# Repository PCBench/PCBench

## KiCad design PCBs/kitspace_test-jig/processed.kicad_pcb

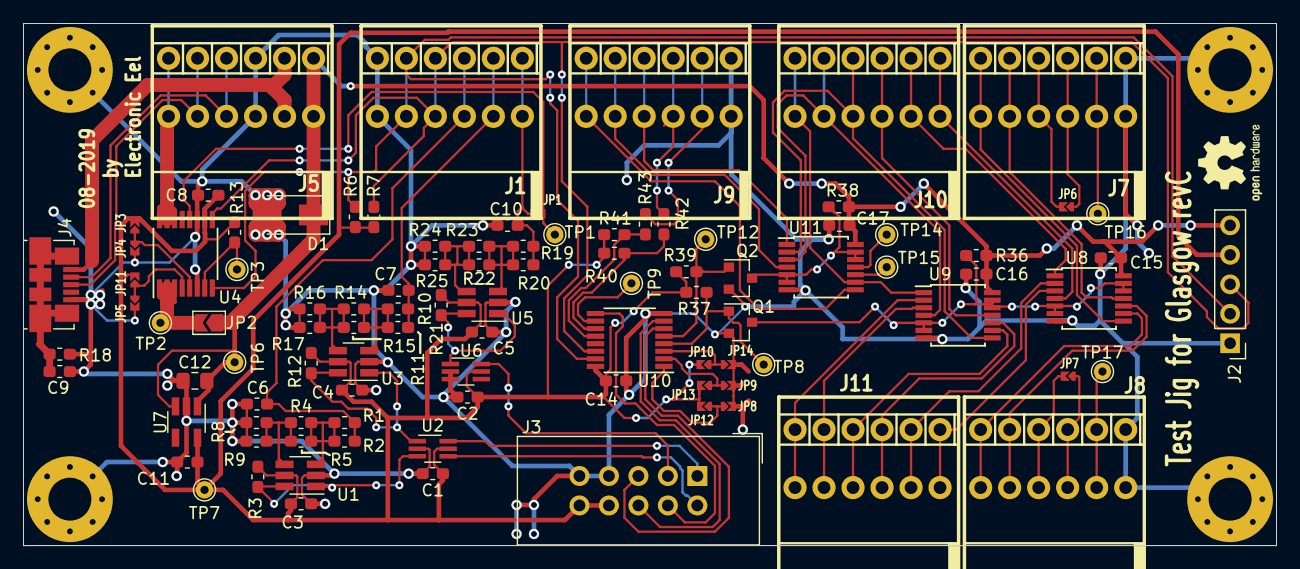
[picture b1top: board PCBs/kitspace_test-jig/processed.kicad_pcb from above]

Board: 2 copper layers, 108.0 x 45.0 mm, 103 parts (0 on the bottom side), 72 nets.

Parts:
C1, C2, C3, C4, C5, C6, C7, C8, C9, C10, C14, C15, C16, C17: 100nF; C_0603_1608Metric_Pad1.05x0.95mm_HandSolder
C11: 1µF; C_0603_1608Metric_Pad1.05x0.95mm_HandSolder
C12: 4.7µF; C_0805_2012Metric_Pad1.15x1.40mm_HandSolder
D1: SMAJ5A; D_SMA
H1, H2, H3, H4: MountingHole_Pad; MountingHole_3.7mm_Pad_Via
J1, J5, J7, J8, J9, J10, J11: AST04106; TerminalBlock_MetzConnect_AST04106_1x06_Lever_Clamp_45Degree
J2: DNP; PinHeader_1x05_P2.54mm_Vertical
J3: Conn_02x05_Odd_Even; IDC-Header_2x05_P2.54mm_Vertical
J4: USB_B_Micro; USB_Micro-B_Molex_47346-0001
JP1, JP4, JP5, JP6, JP7, JP8, JP9, JP10: SolderJumper_2_Bridged; Solderbridge-small-2pad
JP2: SolderJumper_2_Bridged; SolderJumper-2_P1.3mm_Open_TrianglePad1.0x1.5mm
JP3, JP11, JP12, JP13, JP14: SolderJumper_2_Open; Solderbridge-small-2pad
Q1, Q2: BSS138; SOT-23
R1: 5M1; R_0603_1608Metric_Pad1.05x0.95mm_HandSolder
R2: 68k; R_0603_1608Metric_Pad1.05x0.95mm_HandSolder
R3, R12, R13, R21: 4k7; R_0603_1608Metric_Pad1.05x0.95mm_HandSolder
R4, R8, R16, R22, R24, R40, R41, R42, R43: DNP; R_0603_1608Metric_Pad1.05x0.95mm_HandSolder
R5: 910R; R_0603_1608Metric_Pad1.05x0.95mm_HandSolder
R6, R7: 22k; R_0603_1608Metric_Pad1.05x0.95mm_HandSolder
R9: 33k; R_0603_1608Metric_Pad1.05x0.95mm_HandSolder
R10: 91k; R_0603_1608Metric_Pad1.05x0.95mm_HandSolder
R11: 3M6; R_0603_1608Metric_Pad1.05x0.95mm_HandSolder
R14: 1k; R_0603_1608Metric_Pad1.05x0.95mm_HandSolder
R15: 470R; R_0603_1608Metric_Pad1.05x0.95mm_HandSolder
R17: 12k; R_0603_1608Metric_Pad1.05x0.95mm_HandSolder
R18: 1M; R_0603_1608Metric_Pad1.05x0.95mm_HandSolder
R19: 510k; R_0603_1608Metric_Pad1.05x0.95mm_HandSolder
R20: 110k; R_0603_1608Metric_Pad1.05x0.95mm_HandSolder
R23: 680; R_0603_1608Metric_Pad1.05x0.95mm_HandSolder
R25: 7k5; R_0603_1608Metric_Pad1.05x0.95mm_HandSolder
R36, R38: 2k2; R_0603_1608Metric_Pad1.05x0.95mm_HandSolder
R37, R39: 100K; R_0603_1608Metric_Pad1.05x0.95mm_HandSolder
TP1, TP2, TP3, TP6, TP7, TP8, TP9, TP12, TP14, TP15, TP16, TP17: TestPoint; TestPoint_THTPad_D1.5mm_Drill0.7mm
U1, U3, U5: TPS3700; SOT-23-6_Handsoldering
U2, U6: 74LVC2G14; SOT-363_SC-70-6_Handsoldering
U4: INA260; TSSOP-16_4.4x5mm_P0.65mm
U7: AP2127K-3.3; SOT-23-5_HandSoldering
U8, U9, U11: 74HC4066; TSSOP-14_4.4x5mm_P0.65mm
U10: TCA9534; TSSOP-16_4.4x5mm_P0.65mm

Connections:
+3V3: C1.1, C2.1, C3.1, C4.1, C5.1, C8.1, C11.1, C14.1, J2.4, J3.8, J3.10, JP3.2, JP10.2, JP11.2, JP12.2, JP13.2, R3.1, R6.1, R7.1, R12.1, R13.1, R21.1, R37.1, R39.1, R40.2, R41.2, TP7.1, U1.5, U2.5, U3.5, U4.10, U5.5, U6.5, U7.5, U10.16
/DUT_Supply: J5.6, U4.14, U4.15, U4.16
/LED_1V2: J3.2, U2.4
/LED_3V3: J3.1, U2.6
/LED_5V: J3.3, U6.6
/LED_FAIL: J3.6, U10.7
/LED_PASS: J3.5, U10.6
/LED_RUN: J3.4, U10.9
/SCL: J1.4, J2.3, R7.2, U4.9, U10.14
/SDA: J1.5, J2.2, R6.2, U4.8, U10.15
/TP_1V2: C6.1, J1.3, R1.1, R2.1
/TP_3V3: C7.1, J1.2, R10.1, R11.1
/TP_5V: C10.1, J1.1, JP1.1, R19.1, R20.1
/port-connection/Aux_conn_ctrl_5V: Q2.3, R38.2, U11.5, U11.6, U11.12, U11.13
/port-connection/JIG_GPIO0: J9.3, R42.2
/port-connection/JIG_GPIO1: J9.2, R43.2
/port-connection/Port_conn_ctrl_5V: Q1.3, R36.2, U8.5, U8.6, U8.12, U8.13, U9.5, U9.6, U9.12, U9.13
/port-connection/TP_A0: J10.6, U9.1, U11.9
/port-connection/TP_A1: J10.5, U9.4, U11.3
/port-connection/TP_A2: J10.4, U9.8, U11.2
/port-connection/TP_A3: J10.3, U9.11
/port-connection/TP_A4: J10.2, U8.1
/port-connection/TP_A5: J10.1, U8.4
/port-connection/TP_A6: J7.6, U8.8
/port-connection/TP_A7: J7.5, U8.11
/port-connection/TP_A_Vio: J7.4, JP6.2
/port-connection/TP_A_Vsns: J7.3, JP6.1
/port-connection/TP_Aux_A10: J9.5, U11.4
/port-connection/TP_Aux_C9: J9.4, U11.1
/port-connection/TP_B0: J11.6, U9.2
/port-connection/TP_B1: J11.5, U9.3
/port-connection/TP_B2: J11.4, U9.9
/port-connection/TP_B3: J11.3, U9.10
/port-connection/TP_B4: J11.2, U8.2
/port-connection/TP_B5: J11.1, U8.3
/port-connection/TP_B6: J8.6, U8.9
/port-connection/TP_B7: J8.5, U8.10
/port-connection/TP_B_Vio: J8.4, JP7.2
/port-connection/TP_B_Vsns: J8.3, JP7.1
/port-connection/TP_Sync: J9.6, U11.8
/port-connection/~Aux_conn_ctrl: Q2.1, R39.2, TP12.1, U10.5
/port-connection/~Port_conn_ctrl: Q1.1, R37.2, TP8.1, U10.4
GND: C1.2, C2.2, C3.2, C4.2, C5.2, C6.2, C7.2, C8.2, C9.2, C10.2, C11.2, C12.2, C14.2, C15.2, C16.2, C17.2, D1.2, H1.1, H2.1, H3.1, H4.1, J1.6, J2.1, J3.7, J3.9, J4.5, J5.3, J7.1, J8.1, J9.1, JP4.2, JP5.2, JP8.2, JP9.2, JP14.2, Q1.2, Q2.2, R8.2, R9.2, R16.2, R17.2, R18.2, R24.2, R25.2, U1.2, U2.2, U3.2, U4.6, U4.11, U5.2, U6.2, U6.3, U7.2, U8.7, U9.7, U10.8, U11.7
unnamed: C9.1, J4.6, R18.1
unnamed: J4.1, J5.2
unnamed: J4.2, J5.4
unnamed: J4.3, J5.5
unnamed: J7.2, TP16.1
unnamed: J8.2, TP17.1
unnamed: JP1.2, TP1.1, U4.12
unnamed: JP2.2, TP2.1, U4.1, U4.2, U4.3
unnamed: JP3.1, JP4.1, U4.5
unnamed: JP10.1, JP14.1, U10.3
unnamed: JP5.1, JP11.1, U4.4
unnamed: JP8.1, JP12.1, U10.1
unnamed: JP9.1, JP13.1, U10.2
unnamed: R1.2, R2.2, R4.1, R5.1, U1.3
unnamed: R3.2, U1.1, U1.6, U2.3
unnamed: R4.2, R5.2, R8.1, R9.1, U1.4
unnamed: R10.2, R11.2, R14.1, R15.1, U3.3
unnamed: R12.2, U2.1, U3.1, U3.6
unnamed: R13.2, TP3.1, U4.7
unnamed: R14.2, R15.2, R16.1, R17.1, U3.4
unnamed: R19.2, R20.2, R22.1, R23.1, U5.3
unnamed: R21.2, U5.1, U5.6, U6.1
unnamed: R22.2, R23.2, R24.1, R25.1, U5.4
unnamed: R40.1, R42.1, U10.11
unnamed: R41.1, R43.1, U10.12
unnamed: TP9.1, U10.10
unnamed: TP14.1, U11.11
unnamed: TP15.1, U11.10
VBUS: C12.1, C15.1, C16.1, C17.1, D1.1, J2.5, J5.1, JP2.1, R36.1, R38.1, TP6.1, U7.1, U7.3, U8.14, U9.14, U11.14

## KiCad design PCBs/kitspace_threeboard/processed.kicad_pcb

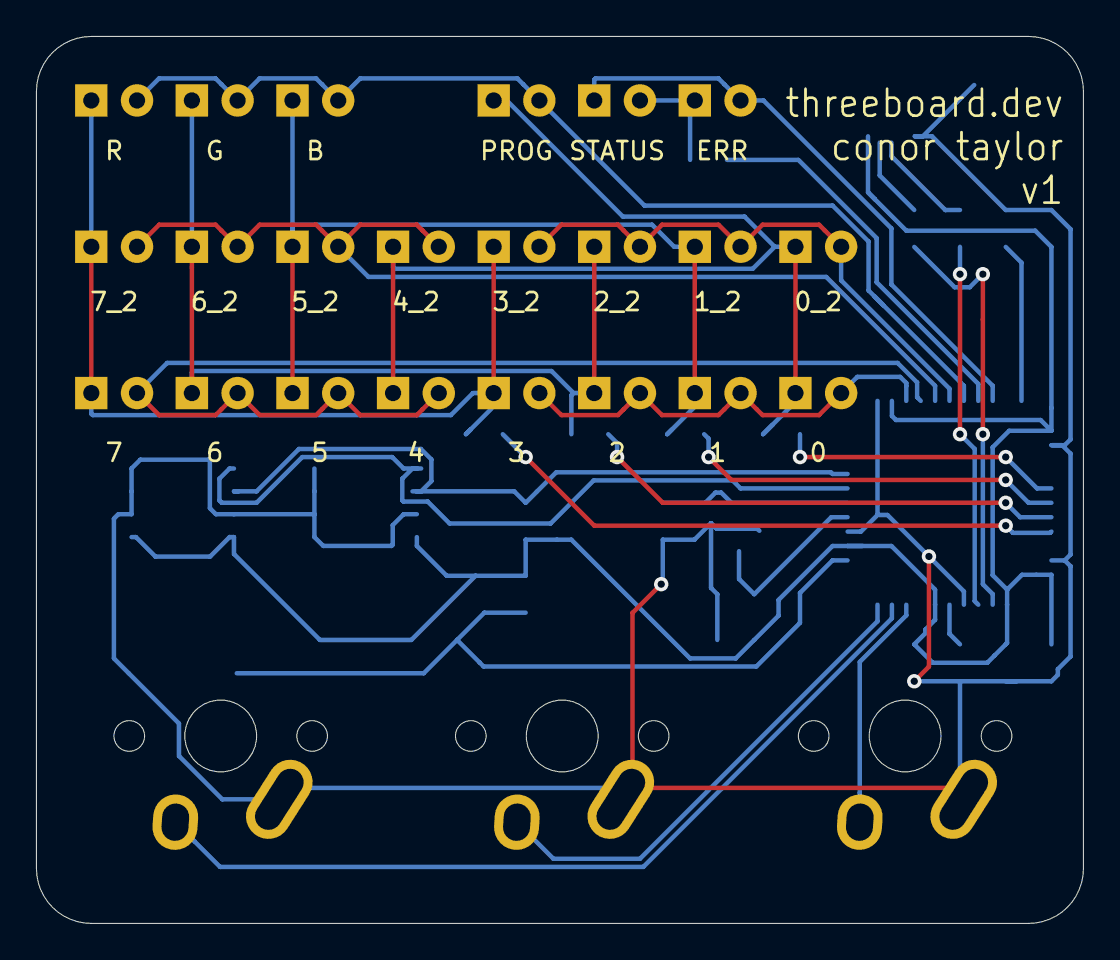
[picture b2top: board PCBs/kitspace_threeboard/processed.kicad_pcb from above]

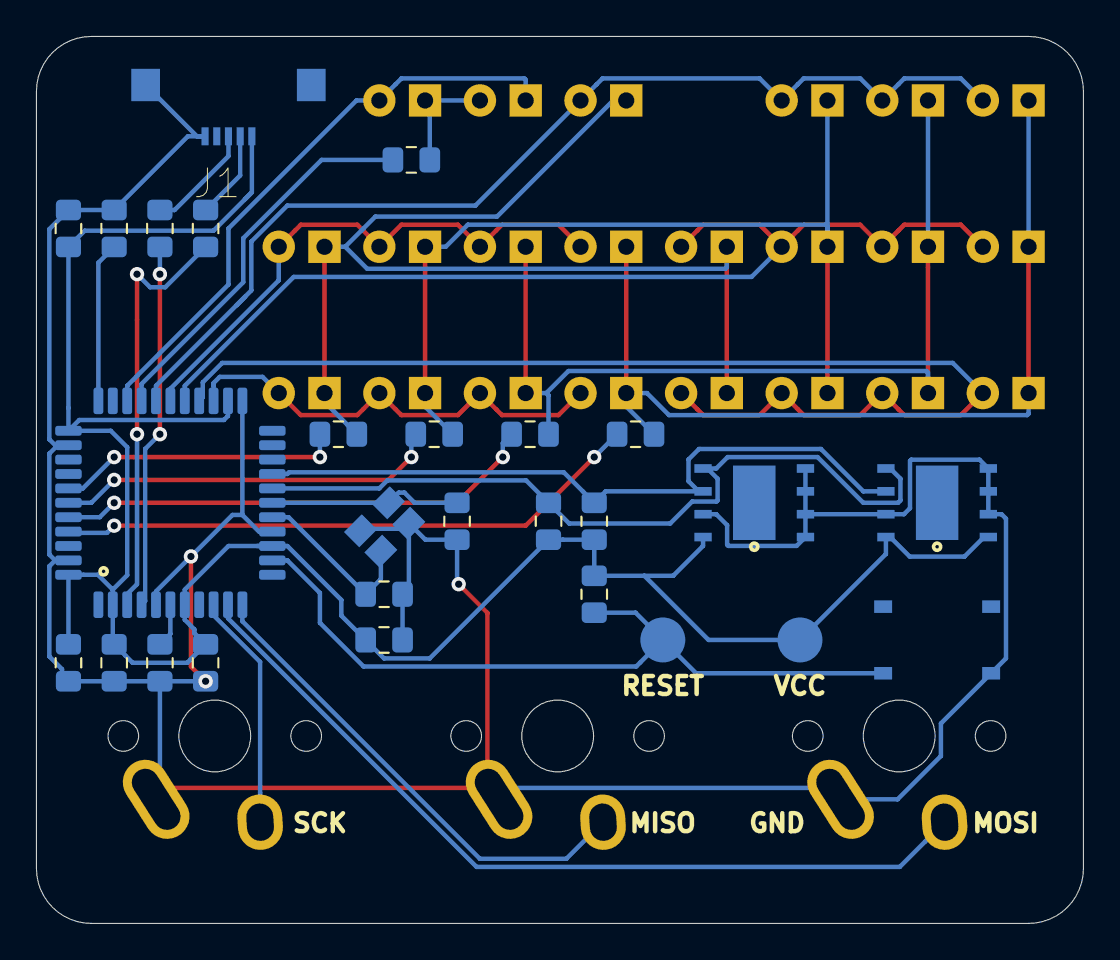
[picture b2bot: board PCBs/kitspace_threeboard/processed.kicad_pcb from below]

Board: 2 copper layers, 58.2 x 49.3 mm, 50 parts (25 on the bottom side), 32 nets.

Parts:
0, 0_2, 1, 1_2, 2, 2_2, 3, 3_2, 4, 4_2, 5, 5_2, 6, 6_2, 7, 7_2: LED; LED_D3.0mm
B: LED; LED_D3.0mm
C1, C2: 22p; C_0805_2012Metric_Pad1.15x1.40mm_HandSolder
C3, C4, C5, C6: 0.1u; C_0805_2012Metric_Pad1.15x1.40mm_HandSolder
C7: 4.7u; C_0805_2012Metric_Pad1.15x1.40mm_HandSolder
C8: 1u; C_0805_2012Metric_Pad1.15x1.40mm_HandSolder
ERR: LED; LED_D3.0mm
G: LED; LED_D3.0mm
J1: USB_mini_micro_B; GCT_USB3070-XX-X_REVE
K1, K2, K3: KEYSW; Mx_Alps_100
PROG: LED; LED_D3.0mm
R: LED; LED_D3.0mm
R1, R2: 10k; R_0805_2012Metric_Pad1.15x1.40mm_HandSolder
R3, R4: 22; R_0805_2012Metric_Pad1.15x1.40mm_HandSolder
R5, R6, R7, R8, R9: 220; R_0805_2012Metric_Pad1.15x1.40mm_HandSolder
R10, R11: 4.7k; R_0805_2012Metric_Pad1.15x1.40mm_HandSolder
STATUS: LED; LED_D3.0mm
SW1: SW_PUSH; SW_PTS526_SK08_SMTR2_LFS
U1: ATMEGA32U4; LQFP-44_10x10mm_P0.8mm
U2, U3: 24LC512; DFN500X600X95-9N
X1: XTAL_GND; crystal_FA238-TSX3225

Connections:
/col0: R5.2, U1.41
/col1: R6.2, U1.40
/col2: R7.2, U1.39
/col3: R8.2, U1.38
/eeprom_scl: R11.2, U1.19, U2.6, U3.6
/eeprom_sda: R10.2, U1.18, U2.5, U3.5
/row0: 4_2.2, 5_2.2, 6_2.2, 7_2.2, U1.27
/row1: 0_2.2, 1_2.2, 2_2.2, 3_2.2, U1.28
/row2: 4.2, 5.2, 6.2, 7.2, U1.26
/row3: 0.2, 1.2, 2.2, 3.2, U1.25
/row4: B.2, G.2, PROG.2, R.2, U1.29
/status0: R9.2, U1.30
/status1: ERR.2, STATUS.1, U1.31
/switch1: K1.2, U1.10
/switch2: K2.2, U1.11
/switch3: K3.2, U1.9
GND: C1.2, C2.2, C3.2, C4.2, C5.2, C6.2, C7.2, C8.2, J1.5, J1.6, K1.1, K2.1, K3.1, R2.1, SW1.1, U1.5, U1.15, U1.23, U1.35, U1.43, U2.2, U2.3, U2.4, U2.7, U3.1, U3.2, U3.3, U3.4, U3.7, X1.3
unnamed: C1.1, U1.16, X1.1
unnamed: C2.1, U1.17, X1.2
unnamed: C8.1, U1.6
unnamed: 3.1, 3_2.1, 7.1, 7_2.1, R.1, R5.1
unnamed: 2.1, 2_2.1, 6.1, 6_2.1, G.1, R6.1
unnamed: 1.1, 1_2.1, 5.1, 5_2.1, B.1, R7.1
unnamed: 0.1, 0_2.1, 4.1, 4_2.1, PROG.1, R8.1
unnamed: ERR.1, R9.1, STATUS.2
unnamed: J1.2, R3.2
unnamed: J1.3, R4.2
unnamed: R1.2, SW1.2, U1.13
unnamed: R2.2, U1.33
unnamed: R3.1, U1.3
unnamed: R4.1, U1.4
VCC: C3.1, C4.1, C5.1, C6.1, C7.1, J1.1, R1.1, R10.1, R11.1, U1.2, U1.7, U1.14, U1.24, U1.34, U1.44, U2.1, U2.8, U3.8

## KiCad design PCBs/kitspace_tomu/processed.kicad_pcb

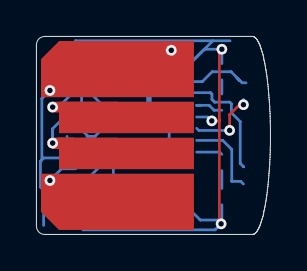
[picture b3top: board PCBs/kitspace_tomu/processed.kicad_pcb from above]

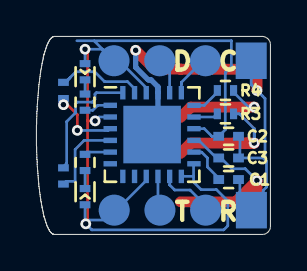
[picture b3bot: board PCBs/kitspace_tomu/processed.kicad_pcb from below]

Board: 2 copper layers, 13.0 x 11.0 mm, 15 parts (14 on the bottom side), 20 nets.

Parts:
C1, C2: 1uF; C_0402
C3: 47uF; C_0402
D1, D2: LED; LED_0402
P1: USART0; debug-points
P2: DEBUG; debug-points
P3: USB-PCB
R1, R2: 75; R_0402
R3, R4: 15; R_0402
U1: EFM32HG309; QFN-24-1EP_5x5mm_Pitch0.65mm
W1: CAP0; minimal-points
W2: CAP1; minimal-points

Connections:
+3V3: C2.1, D1.2, D2.2, P1.4, P2.4, U1.2, U1.9, U1.12, U1.13, U1.16, U1.22
/CAP0A: U1.3, W1.2
/CAP0B: U1.23, W1.1
/CAP1A: U1.4, W2.2
/CAP1B: U1.24, W2.1
/DBG_SWCLK: P2.2, U1.19
/DBG_SWDIO: P2.3, U1.20
/DEC: C1.2, U1.14
/LED0: R2.2, U1.5
/LED1: R1.1, U1.1
/LEU0_RX: P1.2, U1.11
/LEU0_TX: P1.3, U1.10
/RUSB_D+: R4.2, U1.18
/RUSB_D-: R3.2, U1.17
/USB_5V: C3.1, P3.1, U1.15
/USB_D+: P3.3, R4.1
/USB_D-: P3.2, R3.1
GND: C1.1, C2.2, C3.2, P1.1, P2.1, P3.4, U1.21, U1.25
unnamed: D1.1, R1.2
unnamed: D2.1, R2.1

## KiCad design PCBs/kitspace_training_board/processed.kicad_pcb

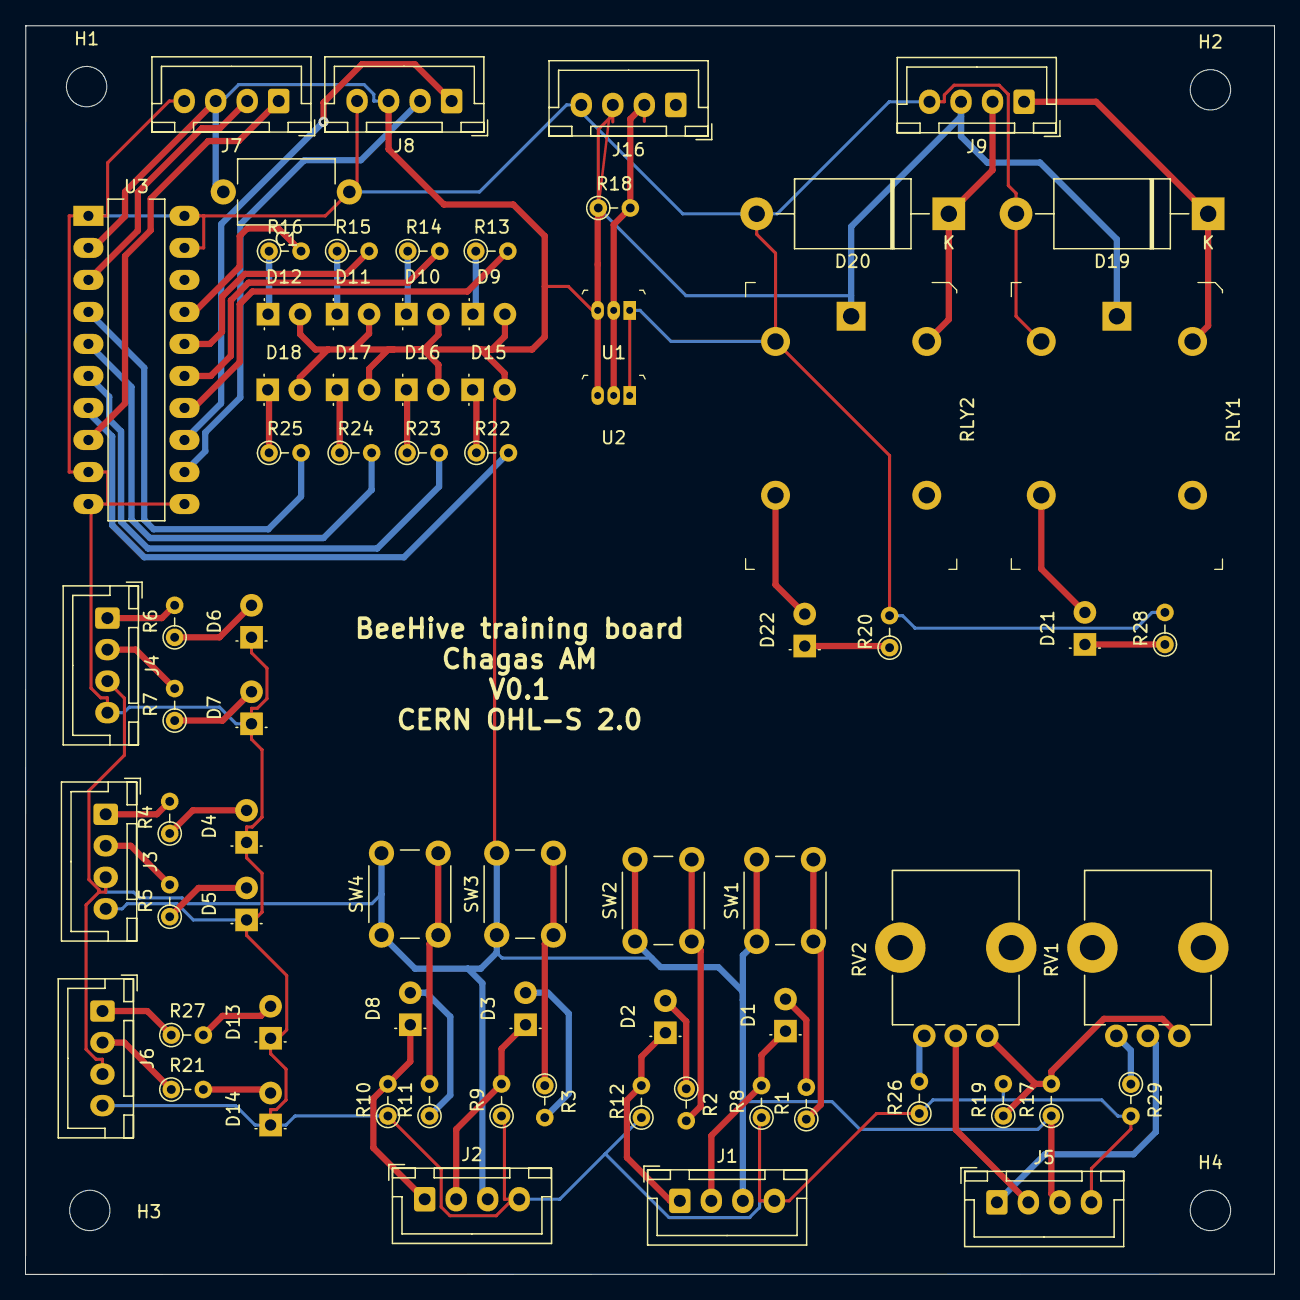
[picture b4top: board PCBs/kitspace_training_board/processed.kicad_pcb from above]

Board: 2 copper layers, 99.1 x 99.1 mm, 77 parts (0 on the bottom side), 58 nets.

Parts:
C1: 100nf; C_Disc_D7.5mm_W5.0mm_P10.00mm
D1, D2, D3, D4, D5, D6, D7, D8, D9, D10, D11, D12, D13, D14, D15, D16, D17, D18, D21, D22: LED; LED_D3.0mm
D19, D20: D_Schottky; D_DO-201AE_P15.24mm_Horizontal
H1, H2, H3, H4: MountingHole; MountingHole_3.2mm_M3_DIN965
J1, J2, J3, J4, J5, J6, J7, J8, J9, J16: Conn_01x04; JST_XH_B4B-XH-A_1x04_P2.50mm_Vertical
R1, R2, R3, R4, R5, R6, R7, R11, R17: 220; R_Axial_DIN0204_L3.6mm_D1.6mm_P2.54mm_Vertical
R8, R9, R10, R12: 1k; R_Axial_DIN0204_L3.6mm_D1.6mm_P2.54mm_Vertical
R13, R14, R15, R16, R20, R21, R22, R23, R24, R25, R27, R28: 560; R_Axial_DIN0204_L3.6mm_D1.6mm_P2.54mm_Vertical
R18: 4.7k; R_Axial_DIN0204_L3.6mm_D1.6mm_P2.54mm_Vertical
R19, R26, R29: 330; R_Axial_DIN0204_L3.6mm_D1.6mm_P2.54mm_Vertical
RLY1, RLY2: G5LE-14_DC5; Relay_THT_G5LE-14
RV1, RV2: 1k; Potentiometer_Alps_RK09K_Single_Vertical
SW1, SW2, SW3, SW4: SW_Push; SW_PUSH_6mm
U1, U2: DS18S20_; TO-92-3
U3: TPIC6595; DIP-20_W7.62mm_LongPads

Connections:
+5V: C1.2, D9.2, D10.2, D11.2, D12.2, D15.2, D16.2, D17.2, D18.2, J1.3, J2.3, J3.3, J4.3, J5.3, J6.3, J7.3, J8.3, J9.3, J16.3, R17.1, R18.1, RLY1.1, RLY2.1, SW1.1, SW2.1, SW3.1, SW4.1, U1.3, U2.3, U3.2
GND: C1.1, D4.1, D5.1, D6.1, D7.1, D13.1, D14.1, D19.2, D20.2, J1.4, J2.4, J3.4, J4.4, J5.4, J6.4, J7.4, J8.4, J9.4, J16.4, R8.1, R9.1, R10.1, R12.1, R19.2, R20.2, R26.1, R28.2, R29.2, RLY1.2, RLY2.2, U1.1, U2.1, U3.1, U3.9, U3.10, U3.11, U3.19, U3.20
unnamed: D1.1, J1.2, R8.2
unnamed: D1.2, R1.2
unnamed: D2.1, J1.1, R12.2
unnamed: D2.2, R2.1
unnamed: D3.1, J2.2, R9.2
unnamed: D3.2, R3.2
unnamed: D4.2, R4.1
unnamed: D5.2, R5.1
unnamed: D6.2, R6.1
unnamed: D7.2, R7.1
unnamed: D8.1, J2.1, R10.2
unnamed: D8.2, R11.1
unnamed: D9.1, R13.1
unnamed: D10.1, R14.1
unnamed: D11.1, R15.1
unnamed: D12.1, R16.1
unnamed: D13.2, R27.2
unnamed: D14.2, R21.2
unnamed: D15.1, R22.1
unnamed: D16.1, R23.1
unnamed: D17.1, R24.1
unnamed: D18.1, R25.1
unnamed: D19.1, J9.1, RLY1.5
unnamed: D20.1, J9.2, RLY2.5
unnamed: D21.1, R28.1
unnamed: D21.2, RLY1.3
unnamed: D22.1, R20.1
unnamed: D22.2, RLY2.3
unnamed: J3.1, R4.2
unnamed: J3.2, R5.2
unnamed: J4.1, R6.2
unnamed: J4.2, R7.2
unnamed: J5.1, RV1.2
unnamed: J5.2, RV2.2
unnamed: J6.1, R27.1
unnamed: J6.2, R21.1
unnamed: J7.1, U3.8
unnamed: J7.2, U3.3
unnamed: J8.1, U3.13
unnamed: J8.2, U3.12
unnamed: J16.2, R18.2, U1.2, U2.2
unnamed: R1.1, SW1.2
unnamed: R2.2, SW2.2
unnamed: R3.1, SW3.2
unnamed: R11.2, SW4.2
unnamed: R13.2, U3.14
unnamed: R14.2, U3.15
unnamed: R15.2, U3.16
unnamed: R16.2, U3.17
unnamed: R17.2, R19.1, RV1.1, RV2.1
unnamed: R22.2, U3.7
unnamed: R23.2, U3.6
unnamed: R24.2, U3.5
unnamed: R25.2, U3.4
unnamed: R26.2, RV2.3
unnamed: R29.1, RV1.3

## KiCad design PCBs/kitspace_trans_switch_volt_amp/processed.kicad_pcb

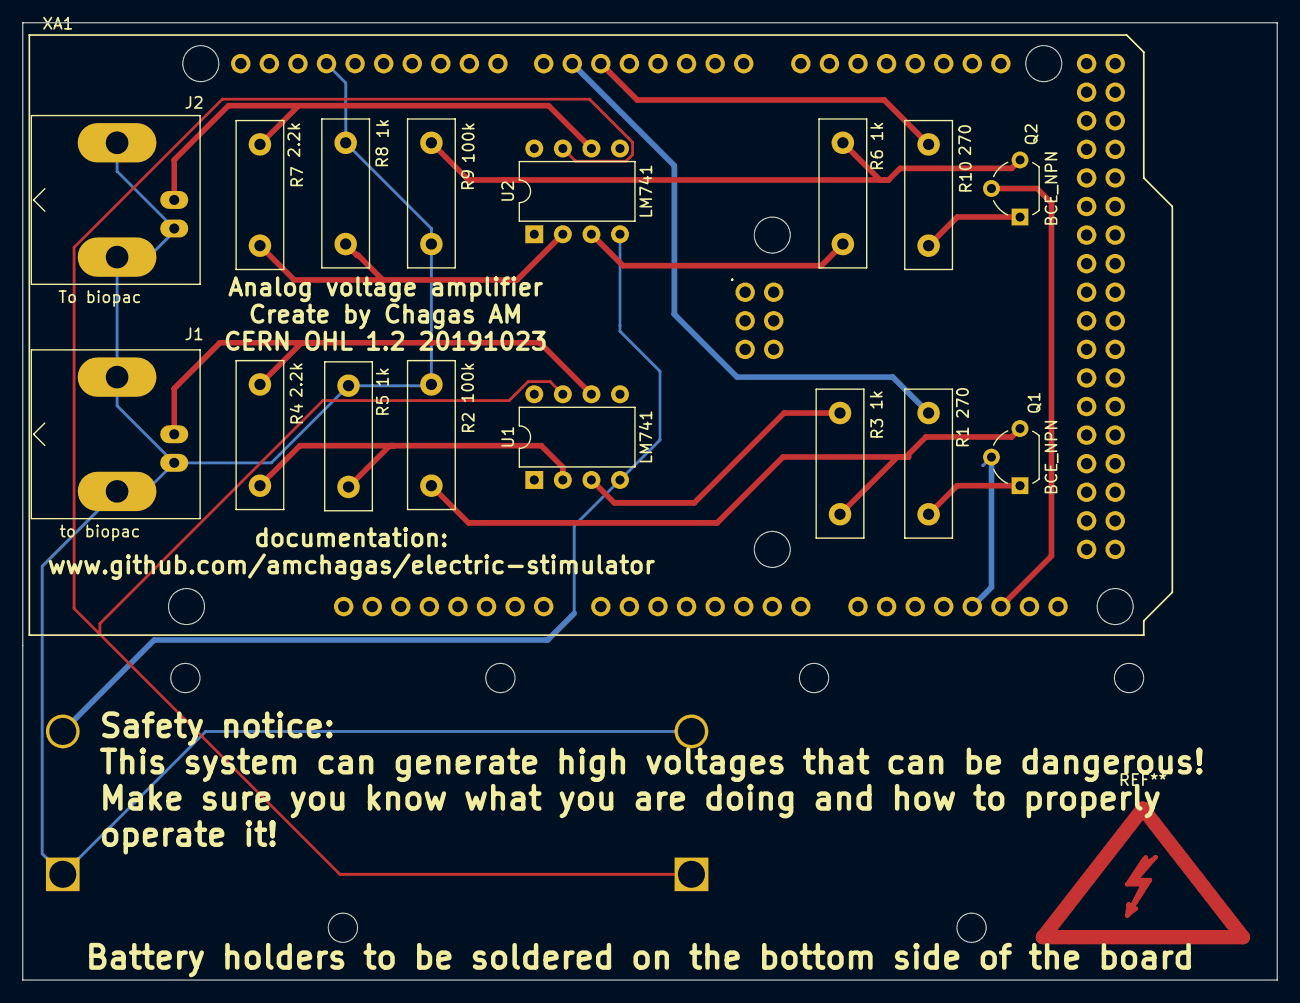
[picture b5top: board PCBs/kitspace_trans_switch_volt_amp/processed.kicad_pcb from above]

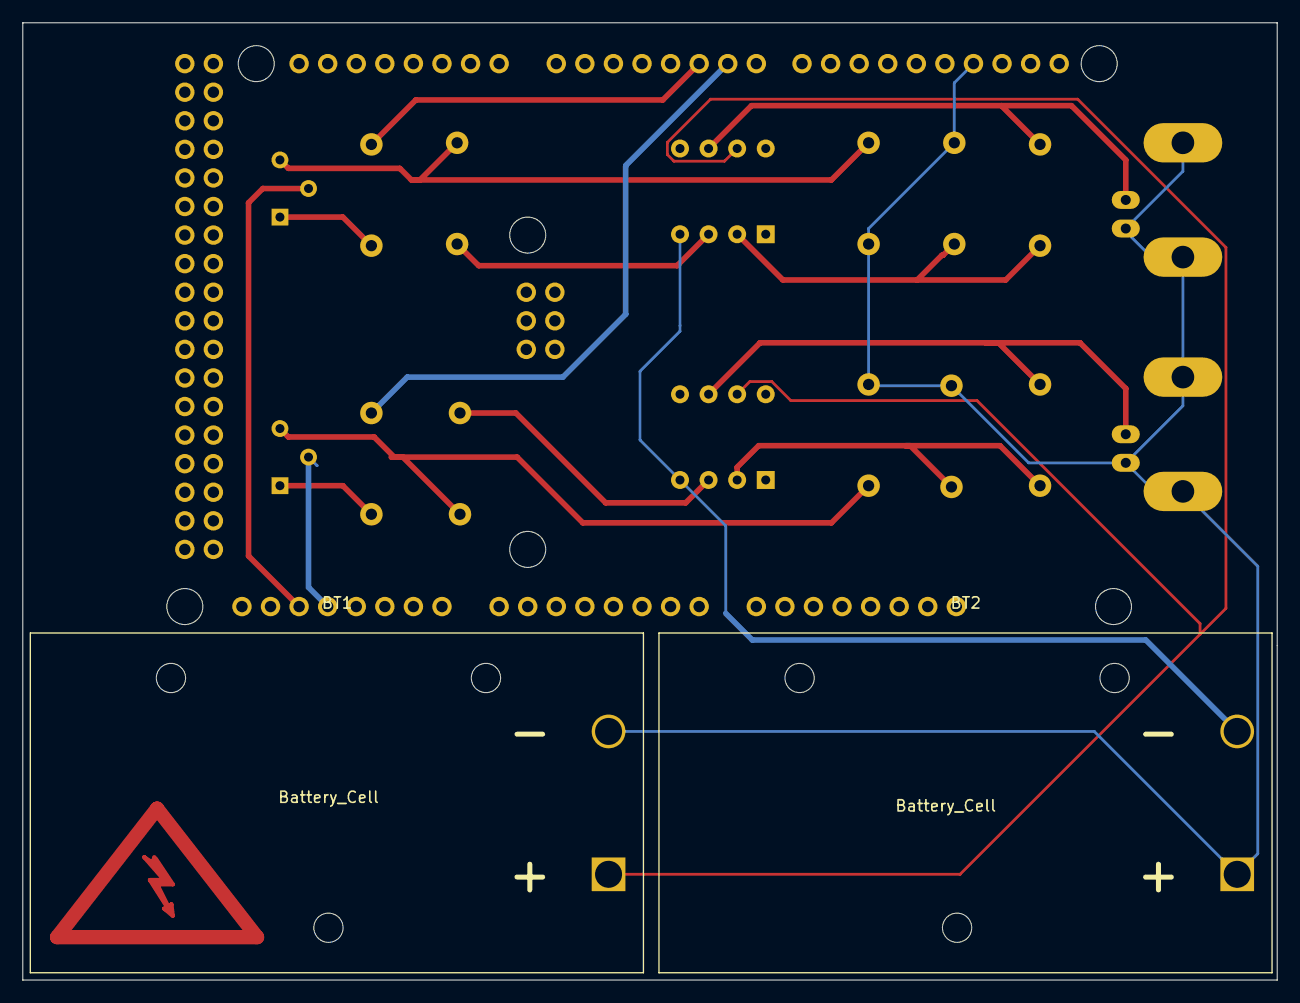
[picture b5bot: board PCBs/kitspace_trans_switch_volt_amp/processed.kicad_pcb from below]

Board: 2 copper layers, 111.5 x 85.1 mm, 19 parts (2 on the bottom side), 17 nets.

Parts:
BT1, BT2: Battery_Cell; BatteryHolder_Eagle_12BH611-GR
J1: to biopac; BNC_Amphenol_B6252HB-NPP3G-50_Horizontal
J2: To biopac; BNC_Amphenol_B6252HB-NPP3G-50_Horizontal
Q1, Q2: BCE_NPN; TO-92L_Wide
R1, R10: 270; R_Box_L13.0mm_W4.0mm_P9.00mm
R2, R9: 100k; R_Box_L13.0mm_W4.0mm_P9.00mm
R3, R5, R6, R8: 1k; R_Box_L13.0mm_W4.0mm_P9.00mm
R4, R7: 2.2k; R_Box_L13.0mm_W4.0mm_P9.00mm
U1, U2: LM741; DIP-8_W7.62mm
XA1: Arduino_Due_Shield

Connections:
GND: BT1.2, BT2.1, J1.2, J2.2, R2.2, R5.1, R8.1, R9.2, XA1.GND1
unnamed: BT1.1, U1.7, U2.7
unnamed: BT2.2, U1.4, U2.4
unnamed: J1.1, R4.2, U1.6
unnamed: J2.1, R7.2, U2.6
unnamed: Q1.1, R1.1
unnamed: Q1.2, XA1.DAC0
unnamed: Q1.3, R2.1, R3.1
unnamed: Q2.1, R10.1
unnamed: Q2.2, XA1.DAC1
unnamed: Q2.3, R6.1, R9.1
unnamed: R1.2, XA1.D6
unnamed: R3.2, U1.3
unnamed: R4.1, R5.2, U1.2
unnamed: R6.2, U2.3
unnamed: R7.1, R8.2, U2.2
unnamed: R10.2, XA1.D5

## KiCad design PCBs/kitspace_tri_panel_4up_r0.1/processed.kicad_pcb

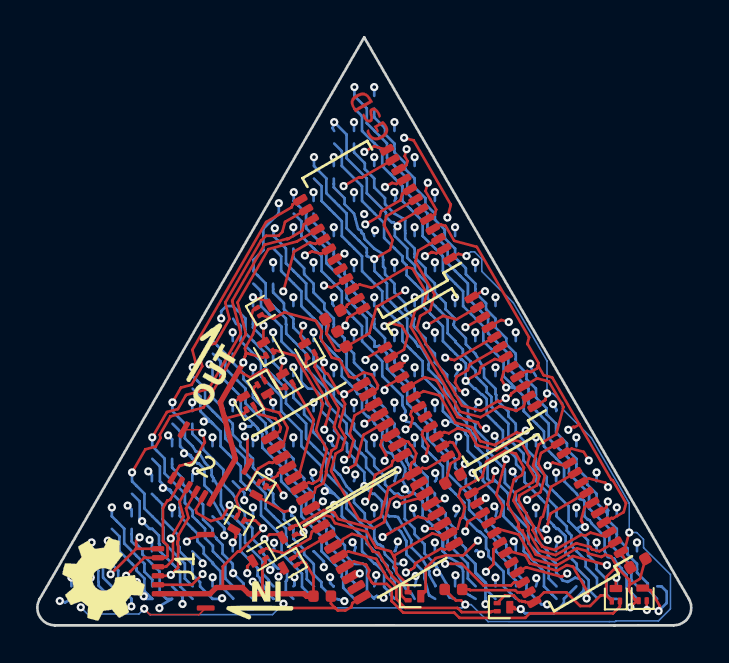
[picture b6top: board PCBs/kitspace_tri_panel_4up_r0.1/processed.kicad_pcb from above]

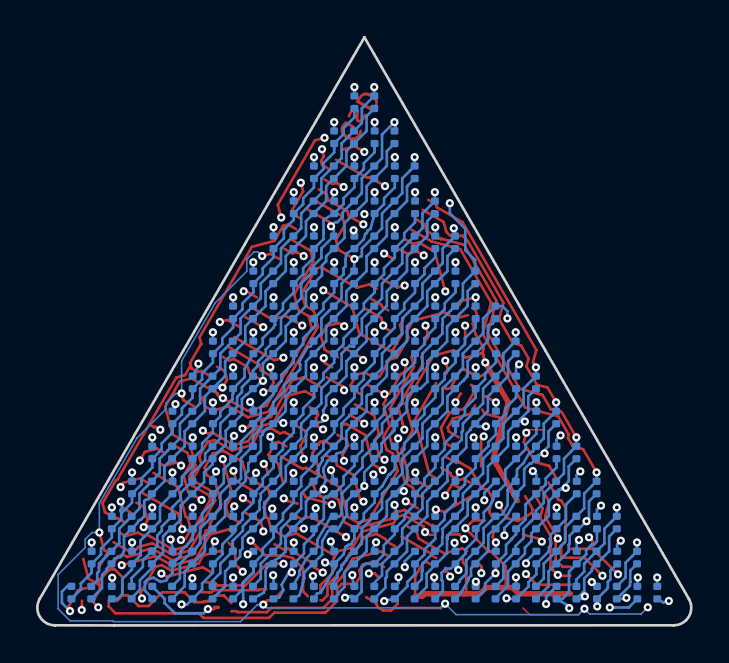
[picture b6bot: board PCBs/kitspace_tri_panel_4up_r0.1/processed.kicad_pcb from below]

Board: 4 copper layers, 36.3 x 32.7 mm, 148 parts (120 on the bottom side), 89 nets.

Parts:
C1, C2, C3: 100nF; C_0402_1005Metric
D1, D2, D3, D4, D5, D6, D7, D8, D9, D10, D11, D12, D13, D14, D15, D17, D18, D19, D20, D21, D22, D23, D24, D25, D26, D27, D28, D29, D30, D33, D34, D35, D36, D37, D38, D39, D40, D41, D42, D43, D44, D45, D49, D50, D51, D52, D53, D54, D55, D56, D57, D58, D59, D60, D65, D66, D67, D68, D69, D70, D71, D72, D73, D74, D75, D81, D82, D83, D84, D85, D86, D87, D88, D89, D90, D97, D98, D99, D100, D101, D102, D103, D104, D105, D113, D114, D115, D116, D117, D118, D119, D120, D129, D130, D131, D132, D133, D134, D135, D145, D146, D147, D148, D149, D150, D161, D162, D163, D164, D165, D177, D178, D179, D180, D193, D194, D195, D209, D210, D225: LED_ARGB; led_rbag_1515_dense
J1: input; 5034800600
J2: output; 5034800600
Q1, Q2, Q3, Q4, Q5, Q6, Q7, Q8, Q9, Q10, Q11, Q12, Q13, Q14, Q15: LP0404N3T5G; SOT-883
R1, R2, R3: R; R_0402_1005Metric
U1, U2, U3: TLC59025; SSOP-24_slim
U4, U5: 74HC595; TSSOP-16_slim

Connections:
U1_r_ext: R1.1, U1.23
U2_r_ext: R2.1, U2.23
U3_r_ext: R3.1, U3.23
blank: J1.3, J2.3, U1.21, U2.21, U3.21
colb_0: D1.4, D17.4, D33.4, D49.4, D65.4, D81.4, D97.4, D113.4, D129.4, D145.4, D161.4, D177.4, D193.4, D209.4, D225.4, U3.5
colb_1: D2.4, D18.4, D34.4, D50.4, D66.4, D82.4, D98.4, D114.4, D130.4, D146.4, D162.4, D178.4, D194.4, D210.4, U3.6
colb_2: D3.4, D19.4, D35.4, D51.4, D67.4, D83.4, D99.4, D115.4, D131.4, D147.4, D163.4, D179.4, D195.4, U3.7
colb_3: D4.4, D20.4, D36.4, D52.4, D68.4, D84.4, D100.4, D116.4, D132.4, D148.4, D164.4, D180.4, U3.8
colb_4: D5.4, D21.4, D37.4, D53.4, D69.4, D85.4, D101.4, D117.4, D133.4, D149.4, D165.4, U3.9
colb_5: D6.4, D22.4, D38.4, D54.4, D70.4, D86.4, D102.4, D118.4, D134.4, D150.4, U3.10
colb_6: D7.4, D23.4, D39.4, D55.4, D71.4, D87.4, D103.4, D119.4, D135.4, U3.11
colb_7: D8.4, D24.4, D40.4, D56.4, D72.4, D88.4, D104.4, D120.4, U3.12
colb_8: D9.4, D25.4, D41.4, D57.4, D73.4, D89.4, D105.4, U3.13
colb_9: D10.4, D26.4, D42.4, D58.4, D74.4, D90.4, U3.14
colb_10: D11.4, D27.4, D43.4, D59.4, D75.4, U3.15
colb_11: D12.4, D28.4, D44.4, D60.4, U3.16
colb_12: D13.4, D29.4, D45.4, U3.17
colb_13: D14.4, D30.4, U3.18
colb_14: D15.4, U3.19
colg_0: D1.3, D17.3, D33.3, D49.3, D65.3, D81.3, D97.3, D113.3, D129.3, D145.3, D161.3, D177.3, D193.3, D209.3, D225.3, U2.5
colg_1: D2.3, D18.3, D34.3, D50.3, D66.3, D82.3, D98.3, D114.3, D130.3, D146.3, D162.3, D178.3, D194.3, D210.3, U2.6
colg_2: D3.3, D19.3, D35.3, D51.3, D67.3, D83.3, D99.3, D115.3, D131.3, D147.3, D163.3, D179.3, D195.3, U2.7
colg_3: D4.3, D20.3, D36.3, D52.3, D68.3, D84.3, D100.3, D116.3, D132.3, D148.3, D164.3, D180.3, U2.8
colg_4: D5.3, D21.3, D37.3, D53.3, D69.3, D85.3, D101.3, D117.3, D133.3, D149.3, D165.3, U2.9
colg_5: D6.3, D22.3, D38.3, D54.3, D70.3, D86.3, D102.3, D118.3, D134.3, D150.3, U2.10
colg_6: D7.3, D23.3, D39.3, D55.3, D71.3, D87.3, D103.3, D119.3, D135.3, U2.11
colg_7: D8.3, D24.3, D40.3, D56.3, D72.3, D88.3, D104.3, D120.3, U2.12
colg_8: D9.3, D25.3, D41.3, D57.3, D73.3, D89.3, D105.3, U2.13
colg_9: D10.3, D26.3, D42.3, D58.3, D74.3, D90.3, U2.14
colg_10: D11.3, D27.3, D43.3, D59.3, D75.3, U2.15
colg_11: D12.3, D28.3, D44.3, D60.3, U2.16
colg_12: D13.3, D29.3, D45.3, U2.17
colg_13: D14.3, D30.3, U2.18
colg_14: D15.3, U2.19
colr_0: D1.2, D17.2, D33.2, D49.2, D65.2, D81.2, D97.2, D113.2, D129.2, D145.2, D161.2, D177.2, D193.2, D209.2, D225.2, U1.5
colr_1: D2.2, D18.2, D34.2, D50.2, D66.2, D82.2, D98.2, D114.2, D130.2, D146.2, D162.2, D178.2, D194.2, D210.2, U1.6
colr_2: D3.2, D19.2, D35.2, D51.2, D67.2, D83.2, D99.2, D115.2, D131.2, D147.2, D163.2, D179.2, D195.2, U1.7
colr_3: D4.2, D20.2, D36.2, D52.2, D68.2, D84.2, D100.2, D116.2, D132.2, D148.2, D164.2, D180.2, U1.8
colr_4: D5.2, D21.2, D37.2, D53.2, D69.2, D85.2, D101.2, D117.2, D133.2, D149.2, D165.2, U1.9
colr_5: D6.2, D22.2, D38.2, D54.2, D70.2, D86.2, D102.2, D118.2, D134.2, D150.2, U1.10
colr_6: D7.2, D23.2, D39.2, D55.2, D71.2, D87.2, D103.2, D119.2, D135.2, U1.11
colr_7: D8.2, D24.2, D40.2, D56.2, D72.2, D88.2, D104.2, D120.2, U1.12
colr_8: D9.2, D25.2, D41.2, D57.2, D73.2, D89.2, D105.2, U1.13
colr_9: D10.2, D26.2, D42.2, D58.2, D74.2, D90.2, U1.14
colr_10: D11.2, D27.2, D43.2, D59.2, D75.2, U1.15
colr_11: D12.2, D28.2, D44.2, D60.2, U1.16
colr_12: D13.2, D29.2, D45.2, U1.17
colr_13: D14.2, D30.2, U1.18
colr_14: D15.2, U1.19
dat: J1.2, U1.2
dat_out: J2.2, U5.9
gnd: C1.2, C2.2, C3.2, J1.6, J1.SH, J2.6, J2.SH, R1.2, R2.2, R3.2, U1.1, U2.1, U3.1, U4.8, U4.13, U5.8, U5.13
latch: J1.4, J2.4, U1.4, U2.4, U3.4, U4.12, U5.12
row_0: D1.1, D2.1, D3.1, D4.1, D5.1, D6.1, D7.1, D8.1, D9.1, D10.1, D11.1, D12.1, D13.1, D14.1, D15.1, Q1.3
row_1: D17.1, D18.1, D19.1, D20.1, D21.1, D22.1, D23.1, D24.1, D25.1, D26.1, D27.1, D28.1, D29.1, D30.1, Q2.3
row_2: D33.1, D34.1, D35.1, D36.1, D37.1, D38.1, D39.1, D40.1, D41.1, D42.1, D43.1, D44.1, D45.1, Q3.3
row_3: D49.1, D50.1, D51.1, D52.1, D53.1, D54.1, D55.1, D56.1, D57.1, D58.1, D59.1, D60.1, Q4.3
row_4: D65.1, D66.1, D67.1, D68.1, D69.1, D70.1, D71.1, D72.1, D73.1, D74.1, D75.1, Q5.3
row_5: D81.1, D82.1, D83.1, D84.1, D85.1, D86.1, D87.1, D88.1, D89.1, D90.1, Q6.3
row_6: D97.1, D98.1, D99.1, D100.1, D101.1, D102.1, D103.1, D104.1, D105.1, Q7.3
row_7: D113.1, D114.1, D115.1, D116.1, D117.1, D118.1, D119.1, D120.1, Q8.3
row_8: D129.1, D130.1, D131.1, D132.1, D133.1, D134.1, D135.1, Q9.3
row_9: D145.1, D146.1, D147.1, D148.1, D149.1, D150.1, Q10.3
row_10: D161.1, D162.1, D163.1, D164.1, D165.1, Q11.3
row_11: D177.1, D178.1, D179.1, D180.1, Q12.3
row_12: D193.1, D194.1, D195.1, Q13.3
row_13: D209.1, D210.1, Q14.3
row_14: D225.1, Q15.3
sclk: J1.5, J2.5, U1.3, U2.3, U3.3, U4.11, U5.11
sdo_U1>sdi_U2: U1.22, U2.2
sdo_U2>sdi_U3: U2.22, U3.2
sdo_U3: U3.22, U4.14
sdo_U4>sdi_U5: U4.9, U5.14
srow_0: Q1.2, U4.15
srow_1: Q2.2, U4.1
srow_2: Q3.2, U4.2
srow_3: Q4.2, U4.3
srow_4: Q5.2, U4.4
srow_5: Q6.2, U4.5
srow_6: Q7.2, U4.6
srow_7: Q8.2, U4.7
srow_8: Q9.2, U5.15
srow_9: Q10.2, U5.1
srow_10: Q11.2, U5.2
srow_11: Q12.2, U5.3
srow_12: Q13.2, U5.4
srow_13: Q14.2, U5.5
srow_14: Q15.2, U5.6
vcc: C1.1, C2.1, C3.1, J1.1, J2.1, Q1.1, Q2.1, Q3.1, Q4.1, Q5.1, Q6.1, Q7.1, Q8.1, Q9.1, Q10.1, Q11.1, Q12.1, Q13.1, Q14.1, Q15.1, U1.24, U2.24, U3.24, U4.10, U4.16, U5.10, U5.16

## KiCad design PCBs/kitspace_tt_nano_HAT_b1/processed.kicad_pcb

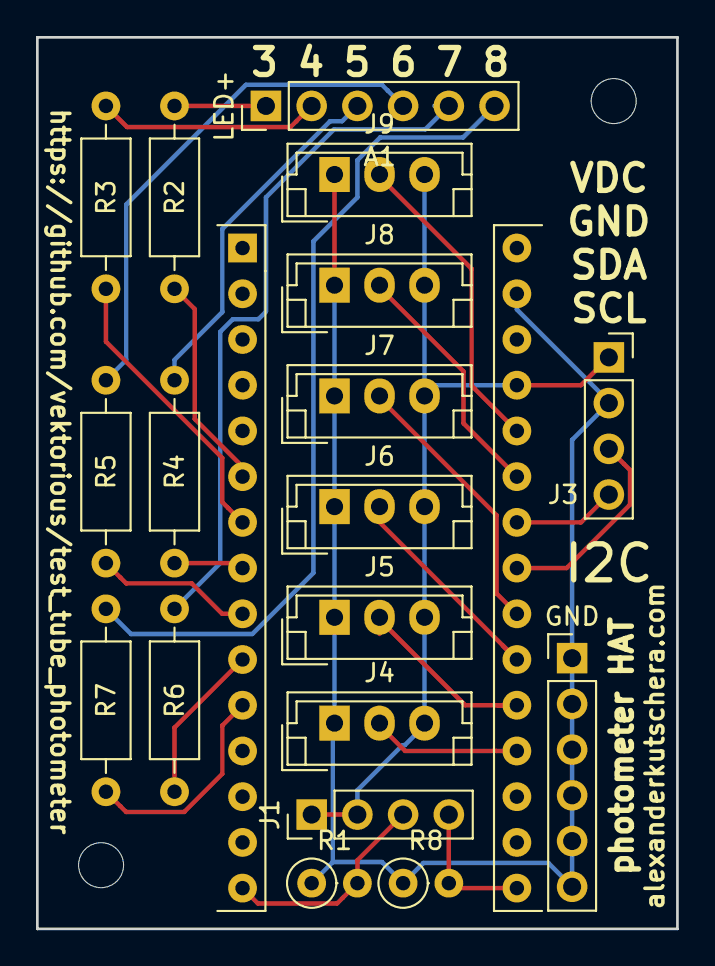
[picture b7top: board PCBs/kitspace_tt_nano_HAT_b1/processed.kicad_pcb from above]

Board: 2 copper layers, 35.6 x 49.5 mm, 19 parts (0 on the bottom side), 24 nets.

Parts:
A1: Arduino_Nano_v3.x; Arduino_Nano2
GND: Conn_01x06_Male; PinHeader_1x06_P2.54mm_Vertical
J1: Conn_01x04_Male; PinHeader_1x04_P2.54mm_Vertical
J3: Conn_01x04_Female; PinSocket_1x04_P2.54mm_Vertical
J4, J5, J6, J7, J8, J9: Conn_01x03_Male; JST_EH_B03B-EH-A_1x03_P2.50mm_Vertical
LED+: Conn_01x06_Male; PinHeader_1x06_P2.54mm_Vertical
R1, R8: R; R_Axial_DIN0207_L6.3mm_D2.5mm_P2.54mm_Vertical
R2, R3, R4, R5, R6, R7: R; R_Axial_DIN0207_L6.3mm_D2.5mm_P10.16mm_Horizontal

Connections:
unnamed: A1.6, R2.1
unnamed: A1.7, R3.1
unnamed: A1.8, R4.1
unnamed: A1.9, R5.1
unnamed: A1.10, R6.1
unnamed: A1.11, R7.1
unnamed: A1.15, J1.3, R1.2
unnamed: A1.16, J1.4, R8.2
unnamed: A1.19, J4.2
unnamed: A1.20, J5.2
unnamed: A1.21, J6.2
unnamed: A1.22, J7.2
unnamed: A1.23, J3.3
unnamed: A1.24, J3.4
unnamed: A1.25, J8.2
unnamed: A1.26, J9.2
unnamed: A1.27, J1.1, J1.2, J3.1, J4.3, J5.3, J6.3, J7.3, J8.3, J9.3
unnamed: A1.29, GND.1, GND.2, GND.3, GND.4, GND.5, GND.6, J3.2, J4.1, J5.1, J6.1, J7.1, J8.1, J9.1, R1.1, R8.1
unnamed: LED+.1, R2.2
unnamed: LED+.2, R3.2
unnamed: LED+.3, R4.2
unnamed: LED+.4, R5.2
unnamed: LED+.5, R6.2
unnamed: LED+.6, R7.2

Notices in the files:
PCBs/kitspace_tomu/processed.kicad_pcb:
License: CC-BY-SA 4.0 or TAPR
PCBs/kitspace_training_board/processed.kicad_pcb:
CERN OHL-S 2.0
PCBs/kitspace_trans_switch_volt_amp/processed.kicad_pcb:
CERN OHL 1.2 20191023
